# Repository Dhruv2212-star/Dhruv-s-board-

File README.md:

The Devboard is divided into the following blocks:  
1. **Block 1 — USB Power Input & Protection**  
2. **Block 2 — 3.3 V Power Supply**  
3. **Block 3 — STM32 Minimum System**  
4. **Block 4 — SWD Programming Interface**  
5. **Block 5 — User Interface**  
6. **Block 6 — GPIO Expansion**  
   ## lets understand why each component was placed and what is it's function block wise
Block 1 — USB Power Input & Protection: Provide safe 5 V input from a USB-C connector and protect the board against faults before supplying the voltage regulator

   | Ref | Component                 | Why it was used                                               | Function                                                      |
| --- | ------------------------- | ------------------------------------------------------------- | ------------------------------------------------------------- |
| J1  | USB-C Receptacle (16-pin) | Standard USB connector for power and future USB communication | Accepts 5 V power from a USB cable                            |
| F1  | MF-R110 Resettable Fuse   | Prevents excessive current from damaging the board            | Disconnects power during overcurrent and automatically resets |
| D1  | ESD9B5.0ST5G TVS Diode    | USB connectors are exposed to electrostatic discharge         | Protects the power input from ESD and voltage spikes          |
| C1  | 10 µF Capacitor           | Bulk input capacitor                                          | Smooths incoming 5 V supply and handles sudden current demand |
| C2  | 100 nF Capacitor          | High-frequency bypass capacitor                               | Filters high-frequency noise on the USB supply                |  

Block 2 — 3.3 V Power Supply: Convert USB 5 V into a stable 3.3 V supply for the STM32 and peripherals  
   
   | Ref | Component        | Why it was used                                                    | Function                                                      |
| --- | ---------------- | ------------------------------------------------------------------ | ------------------------------------------------------------- |
| U1  | AP2112K-3.3 LDO  | Low-noise regulator capable of supplying the STM32 and peripherals | Converts 5 V to regulated 3.3 V                               |
| C3  | 10 µF Capacitor  | Output stability                                                   | Prevents regulator oscillation and supplies transient current |
| C4  | 100 nF Capacitor | High-frequency filtering                                           | Removes switching noise from the regulator output             |

3. Block 3 — STM32 Minimum System: Provide all circuitry required for reliable STM32 operation.  
   
| Ref | Component     | Why it was used         | Function                                       |
| --- | ------------- | ----------------------- | ---------------------------------------------- |
| U2  | STM32F103C8Tx | Main microcontroller    | Executes firmware and controls all peripherals |
| C5  | 100 nF        | Local decoupling        | Filters VDD (Pin 24)                           |
| C6  | 100 nF        | Local decoupling        | Filters VDD (Pin 36)                           |
| C7  | 100 nF        | Local decoupling        | Filters VDD (Pin 48)                           |
| C8  | 100 nF        | Analog supply bypass    | Stabilizes VDDA for ADC and analog peripherals |
| Y1  | 8 MHz Crystal | Accurate external clock | Provides precise system clock reference        |
| C9  | 22 pF         | Crystal load capacitor  | Ensures stable crystal oscillation             |
| C10 | 22 pF         | Crystal load capacitor  | Ensures stable crystal oscillation             |
| R4  | 10 kΩ         | NRST pull-up            | Keeps MCU out of reset during normal operation |
| SW2 | Push Button   | Manual reset            | Pulls NRST low to reset the MCU                |
| R5  | 10 kΩ         | BOOT0 pull-down         | Keeps BOOT0 low for normal Flash boot          |
| SW1 | Push Button   | Bootloader entry        | Pulls BOOT0 high when pressed during reset     |

4. Block 4 — SWD Programming Interface: Allow firmware upload and debugging using an ST-Link programmer  
   
 **Power LED**
| Ref | Component      | Why it was used                           | Function                             |
| --- | -------------- | ----------------------------------------- | ------------------------------------ |
| J2  | 2×5 SWD Header | Standard ARM Cortex programming interface | Connects ST-Link debugger to the MCU |

5. Block 5 — User Interface: Provide simple visual status indication
   
| Ref | Component | Why it was used            | Function                         |
| --- | --------- | -------------------------- | -------------------------------- |
| D2  | Green LED | Indicates board is powered | Lights whenever 3.3 V is present |
| R1  | 1 kΩ      | LED current limiting       | Protects LED and regulator       |

**User LED**
| Ref | Component | Why it was used               | Function                       |
| --- | --------- | ----------------------------- | ------------------------------ |
| D3  | User LED  | Software-controlled indicator | Used for testing and debugging |
| R6  | 330 Ω     | LED current limiting          | Limits current through the LED |  

**UART header**
| Ref | Component | Why it was used               | Function                       |
| --- | --------- | ----------------------------- | ------------------------------ |
| D3  | User LED  | Software-controlled indicator | Used for testing and debugging |
| R6  | 330 Ω     | LED current limiting          | Limits current through the LED |

6. Block 6 — GPIO Expansion: Expose nearly every GPIO pin of the STM32 for external circuits  
   
**Left header**
   | Ref | Component          | Function                                                          |
| --- | ------------------ | ----------------------------------------------------------------- |
| J4  | 1×20 Female Header | Provides access to GPIOs including NRST, BOOT0, PA0–PA7, PB0–PB15 |

**right header**
| Ref | Component          | Function                                                                                  |
| --- | ------------------ | ----------------------------------------------------------------------------------------- |
| J5  | 1×20 Female Header | Provides access to GPIOs including PC13–PC15, PA8–PA15, PB3–PB9, SWD signals, power rails |

# Overall system architecture 
USB-C Input  
     │  
     Resettable Fuse  
     │  
     TVS Protection  
     │  
     Input Capacitors  
     │  
     AP2112K 3.3V Regulator  
     │  
     STM32F103C8T6  
     ├────────────── SWD Header  
     ├────────────── UART Header    
     ├────────────── Power LED  
     ├────────────── Crystal Oscillator  
     ├────────────── Reset Circuit  
     ├────────────── Boot Circuit  
     └────────────── GPIO Headers

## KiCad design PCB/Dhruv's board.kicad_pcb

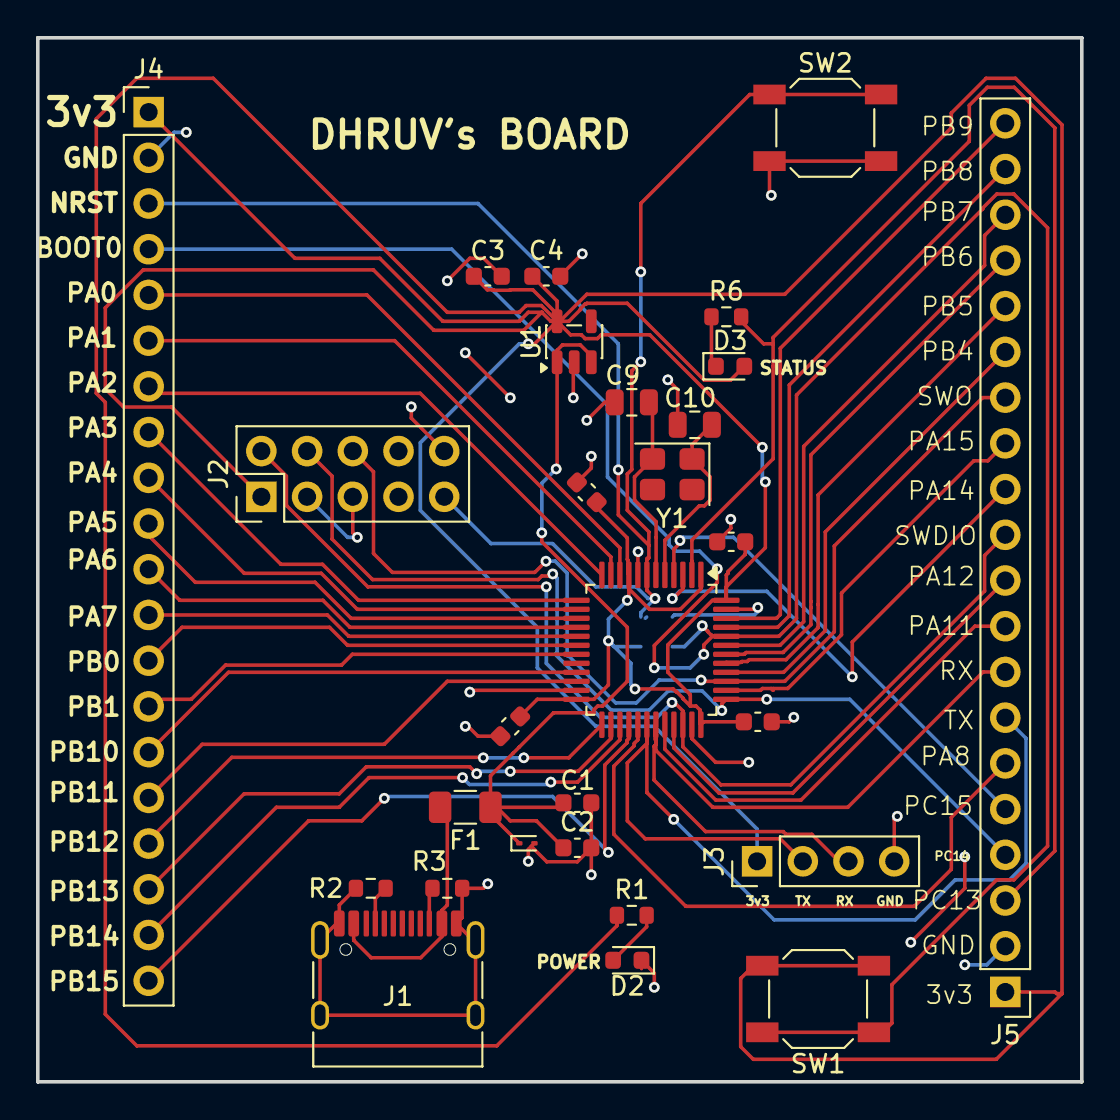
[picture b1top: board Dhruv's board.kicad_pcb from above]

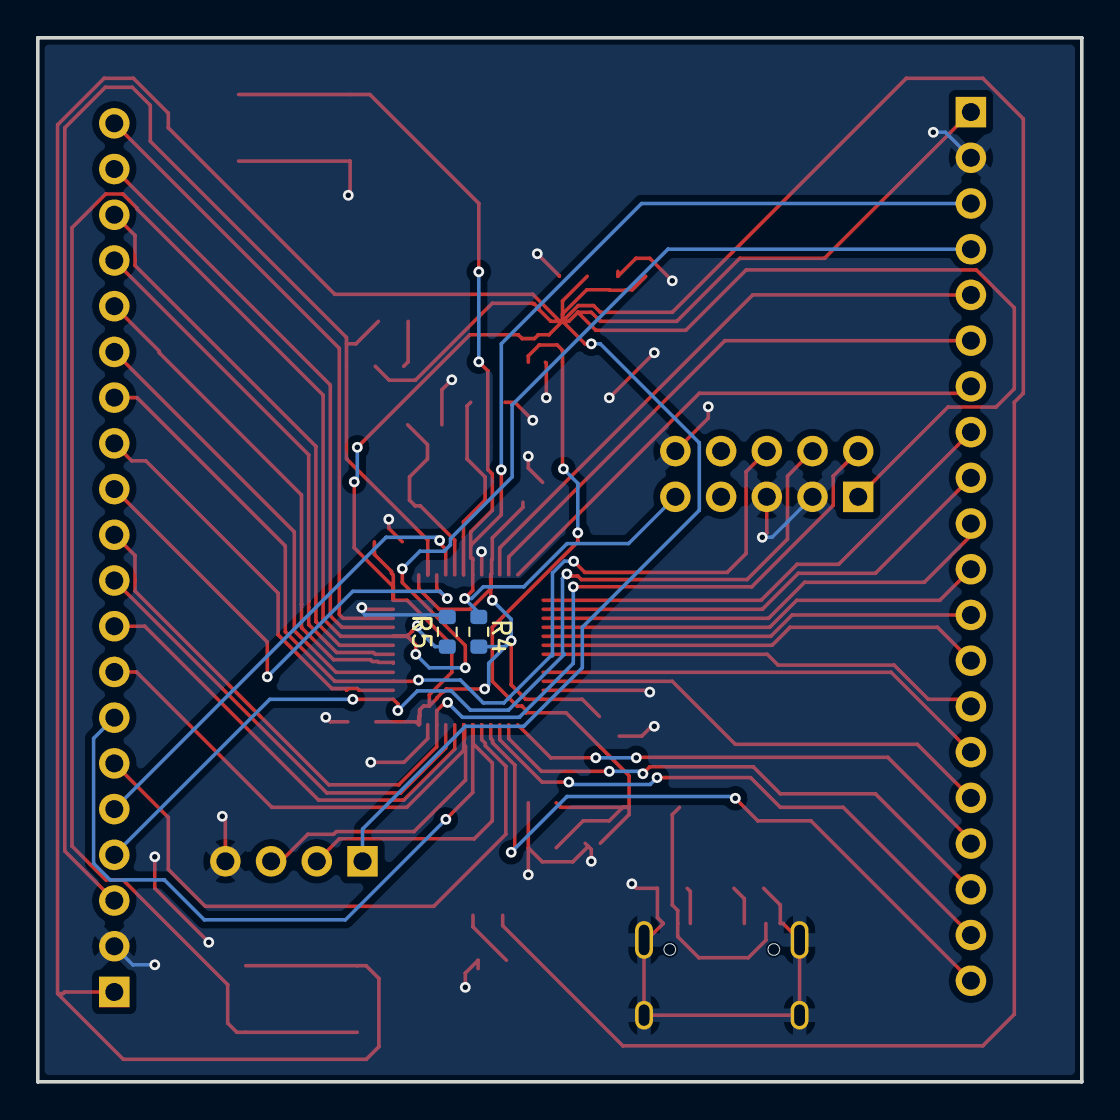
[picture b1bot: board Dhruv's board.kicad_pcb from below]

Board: 2 copper layers, 58.0 x 58.0 mm, 30 parts (2 on the bottom side), 45 nets.

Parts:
C1: 10 µF, X7R, 16 V; C_0603_1608Metric
C2, C4: 100 nF, X7R; C_0603_1608Metric
C3: 10 µF, X7R, 10 V; C_0603_1608Metric
C5, C6, C7, C8: 100 nF; C_0603_1608Metric
C9, C10: 22 pF; C_0805_2012Metric
D1: ESD9B5.0ST5G; D_SOD-923
D2: Power; LED_0603_1608Metric
D3: LED; LED_0603_1608Metric
F1: Bourns MF-R110; Fuse_1206_3216Metric
J1: USB_C_Receptacle_USB2.0_16P; USB_C_Receptacle_HRO_TYPE-C-31-M-12
J2: Conn_02x05_Odd_Even; PinHeader_2x05_P2.54mm_Vertical
J3: Conn_01x04; PinHeader_1x04_P2.54mm_Vertical
J4, J5: Conn_01x20; PinHeader_1x20_P2.54mm_Vertical
R1: 1 kΩ, 1%; R_0603_1608Metric
R2, R3: 5.1 kΩ; R_0603_1608Metric
R4, R5: 10 kΩ; R_0603_1608Metric
R6: 330 Ω; R_0603_1608Metric
SW1, SW2: SW_Push; SW_SPST_SKQG_WithoutStem
U1: AP2112K-3.3; SOT-23-5
U2: STM32F103C8Tx; LQFP-48_7x7mm_P0.5mm
Y1: 8 MHz; Crystal_SMD_3225-4Pin_3.2x2.5mm

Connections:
+3V3: C3.1, C4.1, C5.1, C6.1, C7.1, C8.1, D3.2 (A), J2.1, J3.1, J4.1, J5.1, R1.1, R4.1, SW1.2, U1.5 (VOUT), U2.1 (VBAT), U2.9 (VDDA), U2.24 (VDD), U2.36 (VDD), U2.48 (VDD)
/BOOT0: J4.4, R5.1, SW1.1, U2.44 (BOOT0)
/CC1: J1.A5 (CC1), R2.1
/CC2: J1.B5 (CC2), R3.1
/HSE_IN: C10.1, U2.5 (PD0), Y1.1
/HSE_OUT: C9.1, U2.6 (PD1), Y1.2
/LED_PC13: D3.1 (K), R6.1
/LED_PWR: D2.2 (A), R1.2
/NRST: J2.9, J4.3, R4.2, SW2.1, U2.7 (NRST)
/PA0: J4.5, U2.10 (PA0)
/PA1: J4.6, U2.11 (PA1)
/PA2: J4.7, U2.12 (PA2)
/PA3: J4.8, U2.13 (PA3)
/PA4: J4.9, U2.14 (PA4)
/PA5: J4.10, U2.15 (PA5)
/PA6: J4.11, U2.16 (PA6)
/PA7: J4.12, U2.17 (PA7)
/PA8: J5.6, U2.29 (PA8)
/PA11: J5.9, U2.32 (PA11)
/PA12: J5.10, U2.33 (PA12)
/PA15: J5.13, U2.38 (PA15)
/PB0: J4.13, U2.18 (PB0)
/PB1: J4.14, U2.19 (PB1)
/PB4: J5.15, U2.40 (PB4)
/PB5: J5.16, U2.41 (PB5)
/PB6: J5.17, U2.42 (PB6)
/PB7: J5.18, U2.43 (PB7)
/PB8: J5.19, U2.45 (PB8)
/PB9: J5.20, U2.46 (PB9)
/PB10: J4.15, U2.21 (PB10)
/PB11: J4.16, U2.22 (PB11)
/PB12: J4.17, U2.25 (PB12)
/PB13: J4.18, U2.26 (PB13)
/PB14: J4.19, U2.27 (PB14)
/PB15: J4.20, U2.28 (PB15)
/PC13: J5.3, R6.2, U2.2 (PC13)
/PC14: J2.4, J5.4, J5.12, U2.3 (PC14), U2.37 (PA14)
/PC15: J5.5, U2.4 (PC15)
/SWDIO: J2.2, J5.11, U2.34 (PA13)
/SWO: J2.6, J5.14, U2.39 (PB3)
/UART_RX: J3.3, J5.8, U2.31 (PA10)
/UART_TX: J3.2, J5.7, U2.30 (PA9)
/VBUS_5V: F1.2, J1.A4 (VBUS), J1.A9 (VBUS), J1.B4 (VBUS), J1.B9 (VBUS)
/VIN_5V: C1.1, C2.1, D1.1 (K), F1.1, U1.1 (VIN), U1.3 (EN)
GND: C1.2, C2.2, C3.2, C4.2, C5.2, C6.2, C7.2, C8.2, C9.2, C10.2, D1.2 (A), D2.1 (K), J1.A1 (GND), J1.A12 (GND), J1.B1 (GND), J1.B12 (GND), J1.SH (SHIELD), J2.3, J2.5, J2.10, J3.4, J4.2, J5.2, R2.2, R3.2, R5.2, SW2.2, U1.2 (GND), U2.8 (VSSA), U2.23 (VSS), U2.35 (VSS), U2.47 (VSS)
